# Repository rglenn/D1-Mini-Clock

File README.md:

# D1-Mini-Clock
Shield for D1 Mini boards, providing Stemma QT connector, level-shifting for NeoPixel output, and a battery-backed DS3231 RTC

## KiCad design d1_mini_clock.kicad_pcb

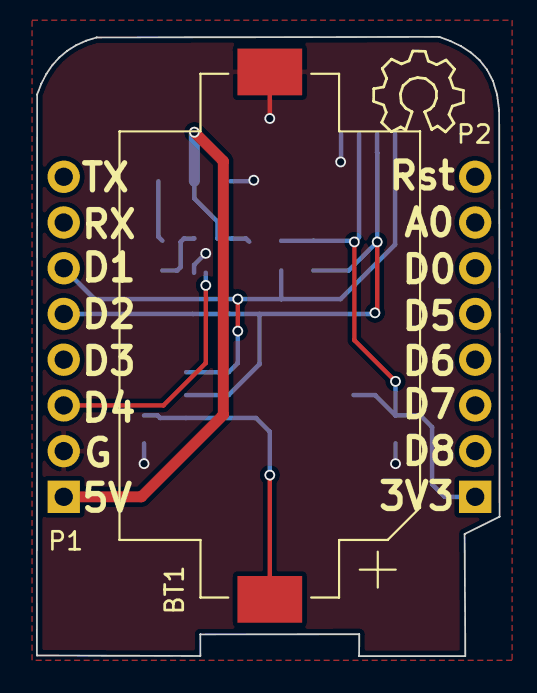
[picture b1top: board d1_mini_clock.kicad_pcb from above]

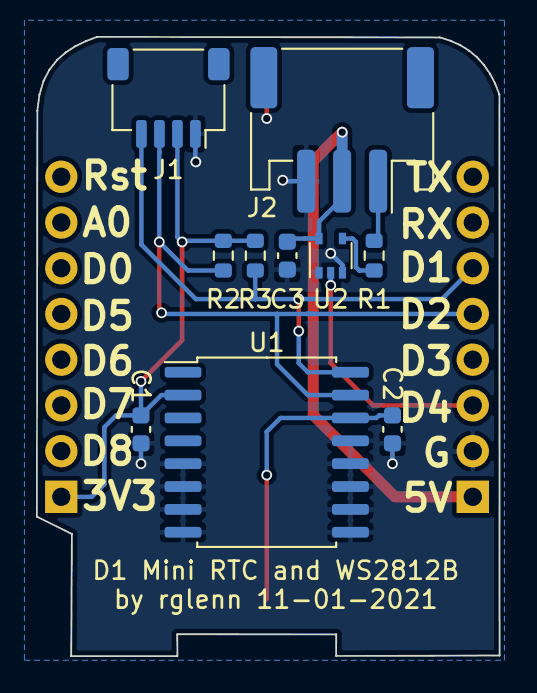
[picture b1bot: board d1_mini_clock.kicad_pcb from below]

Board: 2 copper layers, 25.7 x 34.4 mm, 13 parts (10 on the bottom side), 9 nets.

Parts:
BT1: Battery_Cell; BatteryHolder_Keystone_1060_1x2032
C1, C2, C3: 100n; C_0603_1608Metric
J1: Conn_01x04; JST_SH_SM04B-SRSS-TB_1x04-1MP_P1.00mm_Horizontal
J2: Conn_01x03; JST_PH_S3B-PH-SM4-TB_1x03-1MP_P2.00mm_Horizontal
P1, P2: CONN_01X08; D1_mini_Pin_Header
R1: 100; R_0603_1608Metric
R2, R3: 4.7K; R_0603_1608Metric
U1: DS3231M; SOIC-16W_7.5x10.3mm_P1.27mm
U2: 74AHCT1G125; SOT-353_SC-70-5

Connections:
/+3.3V: C1.1, J1.2, P2.1, R2.2, R3.2, U1.2
/D4: P1.3, U2.2
/SCL: J1.4, P1.6, R3.1, U1.16
/SDA: J1.3, P1.5, R2.1, U1.15
GND: BT1.2, C1.2, C2.2, C3.2, J1.1, J2.3, P1.2, U1.5, U1.6, U1.7, U1.8, U1.9, U1.10, U1.11, U1.12, U1.13, U2.1, U2.3
unnamed: BT1.1, C2.1, U1.14
unnamed: J2.1, R1.1
unnamed: R1.2, U2.4
VCC: C3.1, J2.2, P1.1, U2.5

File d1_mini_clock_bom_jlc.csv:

"Comment","Designator","Footprint","LCSC Part #"
"Battery_Cell","BT1","BatteryHolder_Keystone_1060_1x2032","C70377"
"100n","C3,C1,C2","C_0603_1608Metric","C14663"
"100","R1","R_0603_1608Metric","C22775"
"4.7K","R3,R2","R_0603_1608Metric","C23162"
"DS3231M","U1","SOIC-16W_7.5x10.3mm_P1.27mm","C37663"
"74AHCT1G125","U2","SOT-353_SC-70-5","C12495"

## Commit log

2021-01-11 Adding first PCB rev
2021-01-11 Adding BOM and centroid file
2021-01-11 Correcting inadequate trace width on 5V line.
2021-05-01 Library updates
